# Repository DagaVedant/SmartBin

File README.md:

# smartbin

a sorting head that drops into a normal trash can and puts recyclables in the right side by itself.

demo video: https://www.youtube.com/shorts/8E3T3RMJy3o

demo video: https://www.youtube.com/shorts/8E3T3RMJy3o

## what it does

you drop something on the pan. the load cell feels the weight change, the camera photographs the item, and a small neural net running on a pi zero w decides what it is. a servo tilts the pan and the item slides into the recycling side or the trash side. if the net is not sure, it goes to trash.

## why

- public recycling bins get contaminated really easily
- if enough non-recyclable stuff ends up in one, the facility can reject the whole load, so all of it goes to landfill anyway
- basically every recycling project i've seen is an app that tells *you* which bin to use
- i wanted the bin to just do it, so the person doesn't have to care

## how it works

```
item lands on the pan
   -> load cell reading rises above the threshold and settles
   -> camera captures a frame
   -> numpy cnn returns one of 7 classes plus a confidence
   -> the weight nudges the result (a 600 g "paper" is unlikely)
   -> jurisdiction file maps the class to recycle or trash
   -> below the confidence threshold it goes to trash
   -> "no_object" means a false trigger, so the pan stays level
   -> servo tilts, item slides, pan returns level, scale re-zeroes
   -> event written to sqlite, served as json by a small api
```

| class | bin |
|---|---|
| rigid_plastic, metal, glass, cardboard_paper | recycle |
| soft_plastic_foam, ewaste_hazard, no_object | trash |

the mapping lives in `firmware/config/jurisdiction.yaml`, so a different county's rules are a config change.

## hardware

| part | notes |
|---|---|
| raspberry pi zero w | armv6, 512 mb, no accelerator |
| camera module 3 | imx708, autofocus |
| mg90s servo | gpio12, hardware pwm |
| hx711 + 5 kg bar load cell | data gpio5, clock gpio6 |
| custom hat pcb | in `PCB/` |

the full parts list with prices is `BOM.csv`.

## the board

65 x 45 mm, 2 layers, pi zero hat footprint. fully routed, ground plane poured, drc clean.

| block | parts |
|---|---|
| load cell front end | hx711, pass transistor, feedback divider, 4 caps |
| battery sense | mcp3208 12-bit spi adc, divider, filter |
| servo rail | isolated supply, 470 uf bulk, star ground through one 0r link |
| led ring and break-beam | footprints are on the board but not used in the current build |

- the hx711 runs at 3.3 v, not 5 v, so the gpio can read it without level shifting
- the two grounds meet at exactly one point, so a stalling servo cannot brown out the pi
- the servo is on gpio12 because that pin is a hardware pwm channel

source files are in `PCB/`: `.kicad_pro`, `.kicad_sch`, `.kicad_pcb`, `schematic.pdf`, and `gerbers.zip`.

## the mechanics

all cad is in `CAD/`. `smartbin-head.step` is the full assembly; the parts below are the editable cadquery sources, each with `.py`, `.step` and `.stl`.

| part | job |
|---|---|
| `pan` | the tilting tray the item lands on |
| `pan-hub` | driven side, clamps onto the servo horn |
| `servo-mount` | flat plate the mg90s pushes through, shaft on the pivot axis |
| `bearing-block` | carries the 608zz on the idler side |
| `print-plate` | the mount, hub and block laid out for one print |

`base-plate`, `pan-idler` and `pi-mount` are step-only. `bearing-fit-test` and `bearing-608*` are for checking the bearing fit.

## the classifier

the pi zero w has no tflite or onnx wheels, so the classifier runs in plain numpy from a single `.npz` file (`firmware/smartbin/nn.py` and `firmware/smartbin/graphnet.py`). accuracy matters more than speed here, so the model is the mobilenetv3large at 224 px with batch norm folded into the convolutions and the weights stored as fp16. the numpy version gives the same answers as keras, within 0.011 in probability.

to make it faster, i removed the hidden channels with the smallest weights and then trained the smaller network against the full model (`ml/prune.py`). the model on the bin removes 60 percent of them and runs at 160 px, which cuts the compute from 214m to 69m multiply-adds. a gentler version that removes 50 percent and keeps 224 px is also in the repo.

```
python ml/cache.py --manifest <manifest.csv> --root <dataset root>   decode crops once at 224 px
python ml/export_teacher.py --teacher <teacher.weights.h5>           write firmware/models/smartbin-teacher.npz
python ml/prune.py --ratio 0.6 --size 160 --epochs 20 --out firmware/models/smartbin-fast.npz
python ml/distill.py --teacher <teacher.weights.h5>                  optional, train the small student instead
```

results on the held-out splits (accuracy):

| split | full mobilenetv3large | pruned, 224 px | pruned, 160 px (on the bin) | small student |
|---|---|---|---|---|
| val | 92.2% | 85.9% | 85.1% | 71.3% |
| test, same sources | 91.5% | 84.0% | 81.2% | 69.4% |
| external test, new sources | 65.4% | 62.8% | 63.0% | 51.9% |

the model on the bin is 3.0 mb and takes about 17 ms per image in numpy on a laptop. i have not timed it on the zero w yet, and i expect roughly 2 to 3 seconds per image there. all of the models are in `firmware/models/` and can be selected in `firmware/config/device.yaml`.

## running it on the pi

install the python packages from apt, because a zero w has no wheels for them:

```
sudo apt install git python3-venv python3-numpy python3-pil python3-yaml python3-lgpio \
  python3-picamera2 python3-fastapi python3-uvicorn python3-pydantic python3-pydantic-core
git clone https://github.com/DagaVedant/SmartBin.git ~/SmartBin
python3 -m venv --system-site-packages ~/SmartBin/.venv
```

the servo uses the pi's hardware pwm, so add this to `/boot/firmware/config.txt` and reboot:

```
dtoverlay=pwm,pin=12,func=4
```

then calibrate, once each. the servo needs root because `/sys/class/pwm` is root-only.

```
cd ~/SmartBin/firmware
sudo ~/SmartBin/.venv/bin/python -m smartbin.calibrate servo
~/SmartBin/.venv/bin/python -m smartbin.calibrate scale --grams 47
```

the scale step asks you to empty the pan, then place a known mass (47 g here) on it, and stores the result in `firmware/config/scale_cal.json`.

run it:

```
sudo ~/SmartBin/.venv/bin/python -m smartbin
```

or install it as a service:

```
sudo cp ~/SmartBin/firmware/smartbin.service /etc/systemd/system/
sudo systemctl enable --now smartbin
```

set `hardware: fake` in `firmware/config/device.yaml` to run the whole pipeline on a laptop with fake hardware, and `python -m pytest firmware/tests` to run the tests.

## repo layout

```
CAD/        cadquery sources and step/stl files
PCB/        kicad project, schematic pdf, gerbers.zip
firmware/   the smartbin package, config, model, tests, systemd unit
ml/         distillation pipeline
BOM.csv     parts list
images/     photos and renders
```

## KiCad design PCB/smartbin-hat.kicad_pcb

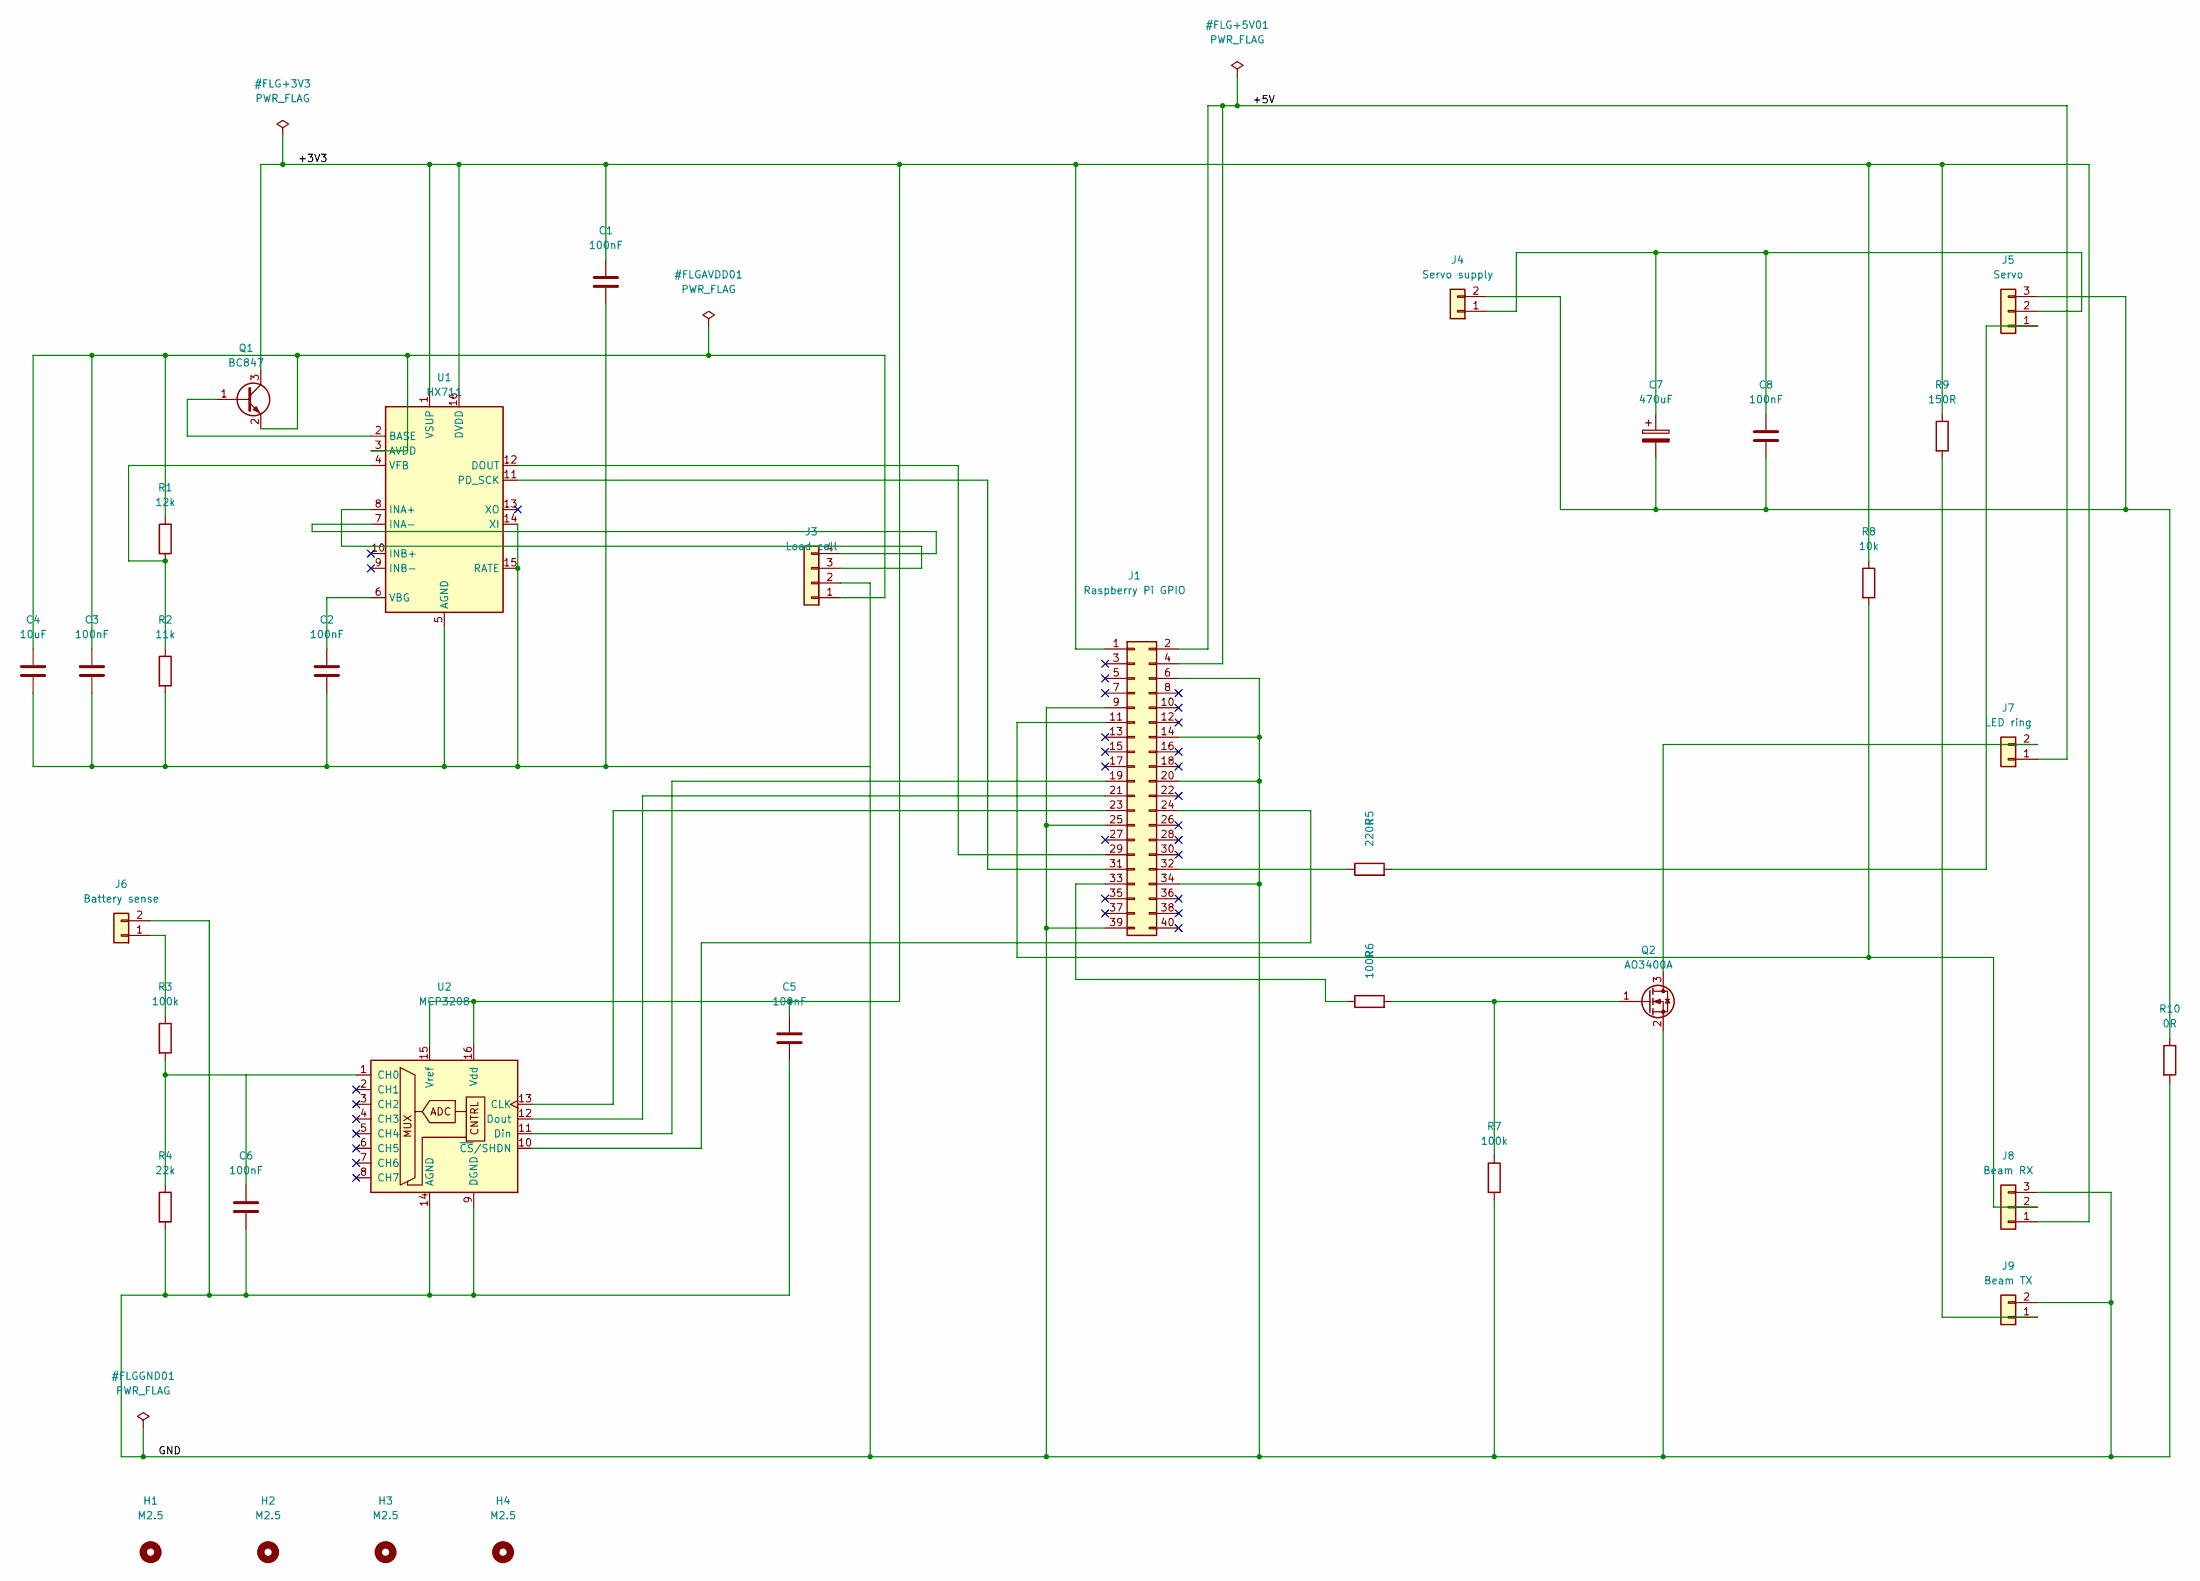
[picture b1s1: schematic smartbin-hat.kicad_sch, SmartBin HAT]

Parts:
C1, C2, C3, C5, C6, C8: 100nF; C_0805_2012Metric
C4: 10uF; C_0805_2012Metric
C7: 470uF; CP_Radial_D8.0mm_P3.50mm
H1, H2, H3, H4: M2.5; MountingHole_2.7mm_M2.5
J1: Raspberry Pi GPIO; PinSocket_2x20_P2.54mm_Vertical
J3: Load cell; PinHeader_1x04_P2.54mm_Vertical
J4: Servo supply; PinHeader_1x02_P2.54mm_Vertical
J5: Servo; PinHeader_1x03_P2.54mm_Vertical
J6: Battery sense; PinHeader_1x02_P2.54mm_Vertical
J7: LED ring; PinHeader_1x02_P2.54mm_Vertical
J8: Beam RX; PinHeader_1x03_P2.54mm_Vertical
J9: Beam TX; PinHeader_1x02_P2.54mm_Vertical
Q1: BC847; SOT-23
Q2: AO3400A; SOT-23
R1: 12k; R_0805_2012Metric
R2: 11k; R_0805_2012Metric
R3, R7: 100k; R_0805_2012Metric
R4: 22k; R_0805_2012Metric
R5: 220R; R_0805_2012Metric
R6: 100R; R_0805_2012Metric
R8: 10k; R_0805_2012Metric
R9: 150R; R_0805_2012Metric
R10: 0R; R_1206_3216Metric
U1: HX711; SOP-16_4.4x10.4mm_P1.27mm
U2: MCP3208; SOIC-16_3.9x9.9mm_P1.27mm

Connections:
+3V3: C1.1, C5.1, J1.1, J8.1, Q1.3 (C), R8.1, R9.1, U1.1 (VSUP), U1.16 (DVDD), U2.15 (Vref), U2.16 (Vdd)
+5V: J1.2, J1.4, J7.1
AVDD: C3.1, C4.1, J3.1, Q1.2 (E), R1.1, U1.3 (AVDD)
AVDD_BASE: Q1.1 (B), U1.2 (BASE)
AVDD_FB: R1.2, R2.1, U1.4 (VFB)
BEAM_RX: J1.11, J8.2, R8.2
BEAM_TX_A: J9.1, R9.2
CELL_A+: J3.3, U1.8 (INA+)
CELL_A-: J3.4, U1.7 (INA-)
GND: C1.2, C2.2, C3.2, C4.2, C5.2, C6.2, J1.6, J1.9, J1.14, J1.20, J1.25, J1.34, J1.39, J3.2, J6.2, J8.3, J9.2, Q2.2 (S), R2.2, R4.2, R7.2, R10.2, U1.5 (AGND), U1.14 (XI), U1.15 (RATE), U2.9 (DGND), U2.14 (AGND)
GND_SERVO: C7.2, C8.2, J4.2, J5.3, R10.1
HX_DOUT: J1.29, U1.12 (DOUT)
HX_SCK: J1.31, U1.11 (PD_SCK)
LED_CATHODE: J7.2, Q2.3 (D)
LED_GATE: Q2.1 (G), R6.2, R7.1
LED_PWM: J1.33, R6.1
SERVO_SIG: J1.32, R5.1
SERVO_SIG_OUT: J5.1, R5.2
SPI_CE0: J1.24, U2.10 (~CS/SHDN)
SPI_MISO: J1.21, U2.12 (Dout)
SPI_MOSI: J1.19, U2.11 (Din)
SPI_SCLK: J1.23, U2.13 (CLK)
VBATT: J6.1, R3.1
VBG: C2.1, U1.6 (VBG)
VSERVO: C7.1, C8.1, J4.1, J5.2

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
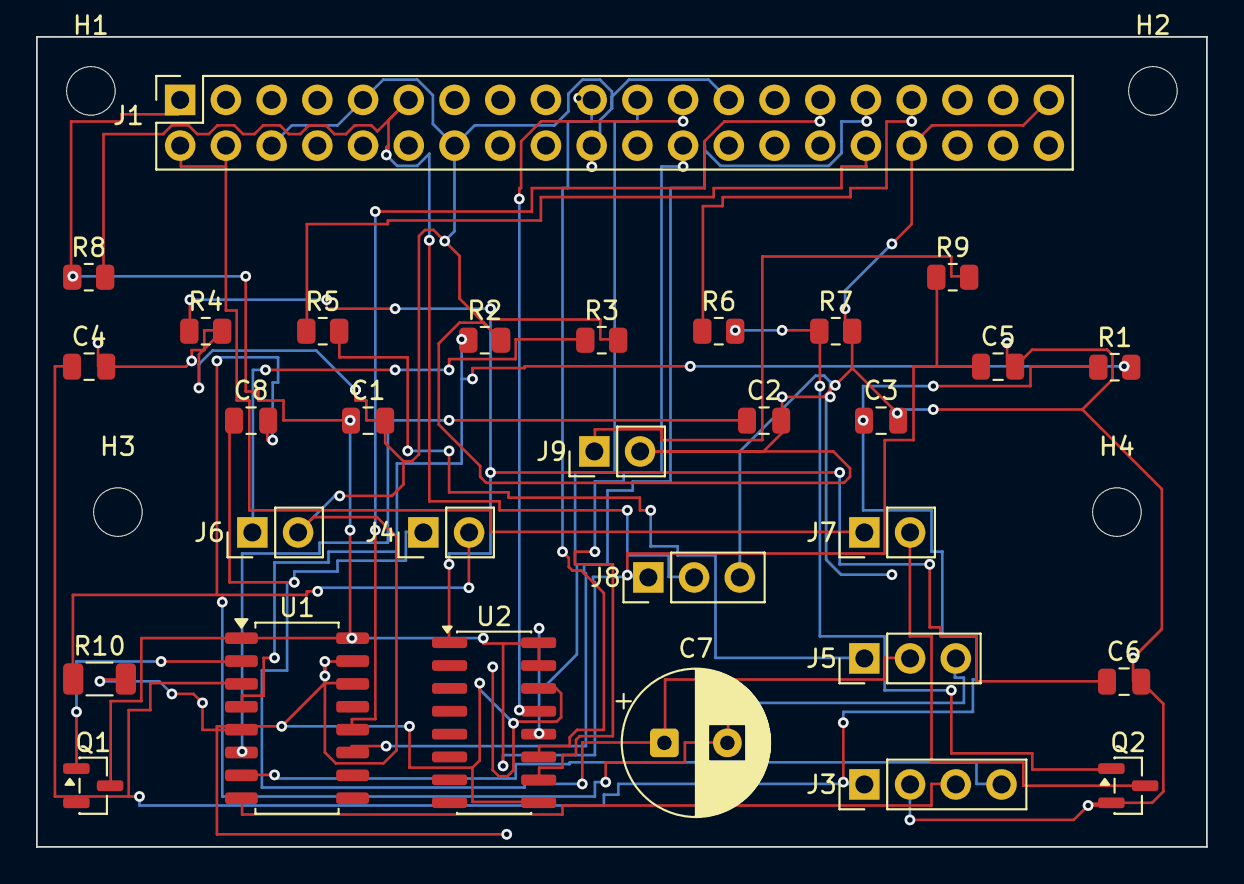
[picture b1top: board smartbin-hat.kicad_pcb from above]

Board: 2 copper layers, 65.0 x 45.0 mm, 34 parts (0 on the bottom side), 26 nets.

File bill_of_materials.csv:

Item,Description,Qty,Unit Price USD,Total USD,Item link,Why I need it,Supplier,Status,Notes
ALREADY OWN,no cost. these are on hand,,,,,,,,
MG996R servo,Metal gear servo. 55g. 25T spline. measured 39.9 x 19.7 x 42.9mm,1,0.00,0.00,N/A,The only actuator in the build. Tilts the pan so the item slides one way or the other,N/A,OWNED,Measured mine with calipers. Body is 39.9mm not the spec 40.7 and the shaft sits 10.95mm off centre. The CAD is built to my unit
Metal servo horn 20mm round,Couples the servo spline to the printed pan hub,1,0.00,0.00,N/A,A 25T spline has 0.74mm teeth which no FDM printer can resolve. The horn is the only thing that can grip the shaft,N/A,OWNED,Ships in the bag with the MG996R
,SUBTOTAL,,,0.00,,,,,
,,,,,,,,,
PARTS I STILL NEED,the funding request,,,,,,,,
Raspberry Pi Zero 2 W,Deployment compute board. 512MB RAM,1,TBD,TBD,TBD,Runs everything - trigger capture classify actuate and log. Idles at 0.4W against the 4B's 2.7W which matters because the Pi can never sleep between items,Raspberry Pi,TO BUY,The one I measured pin 1 on is borrowed from a friend. I need my own for a permanent build
SmartBin HAT PCB,Custom Pi Zero HAT. 2 layer. 65 x 45mm. 1.6mm FR4,1,TBD,TBD,TBD,Everything between the Pi and the mechanism lives on this board. The load cell amp the ADC and the MOSFET are all on it,JLCPCB,TO BUY,Gerbers are exported and DRC clean. TBD until JLCPCB quotes it. A 2 layer board this size is usually a few dollars for five plus shipping
HX711,24-bit bridge ADC for the load cell. SOP-16,1,TBD,TBD,TBD,Reads the load cell. A bare strain gauge puts out microvolts which nothing else in the build can see,LCSC,TO BUY,Runs at 3.3V not 5V so both its signals are directly Pi-safe. That deletes 4 level shifting parts
MCP3208,12-bit SPI ADC. SOIC-16,1,TBD,TBD,TBD,The Pi has no analog input at all. Without this the battery voltage simply cannot be read,LCSC,TO BUY,MCP3008 is pin compatible if 10-bit is good enough
BC847,NPN pass transistor for the HX711 AVDD regulator. SOT-23,1,TBD,TBD,TBD,Generates the analog supply that excites the load cell bridge,LCSC,TO BUY,SOT-23 pinout is base-emitter-collector not BCE. Getting this backwards ships a dead board
AO3400A,Logic-level N-channel MOSFET. SOT-23,1,TBD,TBD,TBD,Switches the LED ring. A Pi GPIO cannot drive an LED ring directly,LCSC,TO BUY,Any logic-level N-FET rated 2A or more works
0805 resistor pack,Assorted 1% 0805 resistors,1,TBD,TBD,TBD,Ten resistors across the whole board - dividers current limits pullups and the star ground link,LCSC,TO BUY,"Values needed: 12k, 11k, 100k x2, 22k, 220R, 100R, 10k, 150R, 0R. The 0R is 1206 not 0805"
100nF 0805 ceramic,Decoupling and filtering,6,TBD,TBD,TBD,Every IC needs local decoupling or it browns out on its own switching noise,LCSC,TO BUY,C1 C2 C3 C5 C6 C8
10uF 0805 ceramic,AVDD bulk. excitation supply for the load cell,1,TBD,TBD,TBD,Holds the analog supply steady while the bridge draws current,LCSC,TO BUY,C4
470uF 16V electrolytic,Bulk capacitance at the servo connector. radial 8mm,1,TBD,TBD,TBD,A servo current spike becomes a brownout without local bulk,LCSC,TO BUY,Mount at the connector NOT at the regulator. The trace between them is what turns a spike into a brownout
2x20 female header 2.54mm,Connects the HAT to the Pi,1,TBD,TBD,TBD,The only mechanical and electrical link between the HAT and the Pi,Amazon,TO BUY,Header position verified against the official Pi Zero 2 W drawing. Pin 1 row confirmed on a physical board
2.54mm pin headers assorted,1x02 x4 / 1x03 x2 / 1x04 x1,1,TBD,TBD,TBD,Every off-board thing plugs in here - load cell servo LED ring break-beam and battery tap,Amazon,TO BUY,Seven connectors total. A strip of breakable header covers all of them
Raspberry Pi Camera Module 3,Top-down camera. 25 x 24mm PCB,1,TBD,TBD,TBD,Takes the photo the classifier runs on. Nothing sorts without it,Raspberry Pi,TO BUY,Mount is not modelled in CAD yet
microSD card 32GB,Pi boot media,1,TBD,TBD,TBD,The Pi has no onboard storage,Amazon,TO BUY,
5kg bar load cell,Weighs the item on the pan. 80 x 12.7 x 12.7mm,1,TBD,TBD,TBD,Weight tells you things a photo cannot - a full drink against an empty can look identical to a camera,Amazon,TO BUY,Check the hole pitch against the printed block before ordering
White LED ring 60mm,Capture illumination. 60mm outer / 44mm inner,1,TBD,TBD,TBD,Consistent lighting so every photo the classifier sees looks the same. Ambient light in a bin varies wildly,Amazon,TO BUY,Retainer is not modelled in CAD yet
IR break-beam sensor pair,Detects an item entering the throat. 5mm barrel,1,TBD,TBD,TBD,The trigger for the whole sequence. Without it the Pi has no idea something arrived,Adafruit 2168 or similar,TO BUY,
608ZZ bearing,Pan pivot on the idler side. 22 OD x 8 ID x 7 W,1,TBD,TBD,TBD,Carries the free end of the pan. Without it the pan hangs off the servo shaft alone and the gearbox takes the load,Amazon,TO BUY,Standard skateboard bearing. The bearing block bore is cut for exactly this
5V 3A power supply,Powers the Pi,1,TBD,TBD,TBD,The Pi never sleeps so this runs continuously,Amazon,TO BUY,
5-6V buck converter,Separate servo rail supply,1,TBD,TBD,TBD,The servo gets its own supply. Sharing a regulator with the Pi means a stalling servo browns out the Pi and corrupts the SD card,Amazon,TO BUY,Must NOT share a regulator with the Pi. The two grounds meet at exactly one 0R link on the board
PETG filament 1kg spool,All seven printed parts including the base plate,1,TBD,TBD,TBD,Every structural part of the mechanism is printed. PETG because it is stiffer and less brittle than PLA,Amazon,TO BUY,About 370g used - 230g for the mechanism plus 140g for the base plate. One spool covers it with plenty spare
M3 x 12mm screws and nuts,Idler flange to pan and pi mount to base plate,4,TBD,TBD,TBD,Holds the idler onto the pan and the Pi mount onto the plate,Hardware,TO BUY,
M4 x 16mm screws and nuts,Servo mount and bearing block to base plate,4,TBD,TBD,TBD,These take the servo reaction torque. Everything else on the plate is along for the ride,Hardware,TO BUY,
M2.5 x 8mm screws,Pi and HAT to the pi mount standoffs,4,TBD,TBD,TBD,Mounts the Pi to the printed standoffs,Hardware,TO BUY,58 x 23mm Pi Zero hole pattern. Standoff bosses are 6mm
M2.5 x 10mm standoffs and screws,Mounts the HAT onto the Pi,4,TBD,TBD,TBD,Keeps the HAT off the Pi so nothing on either board shorts against the other,Hardware,TO BUY,58 x 23mm hole pattern
,SUBTOTAL,,,TBD,,,,,
,,,,,,,,,
TOTAL COST,,,,TBD,,,,TO BUY,Sum of every TO BUY line. Prices and links still need filling in
